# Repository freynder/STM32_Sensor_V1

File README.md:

# STM32 sensors board with RFM69(H)W footprint

First try on designing an STM32 board for running MySensors

## Top view

## Bottom view

## Early prototype top

## Early prototype bottom

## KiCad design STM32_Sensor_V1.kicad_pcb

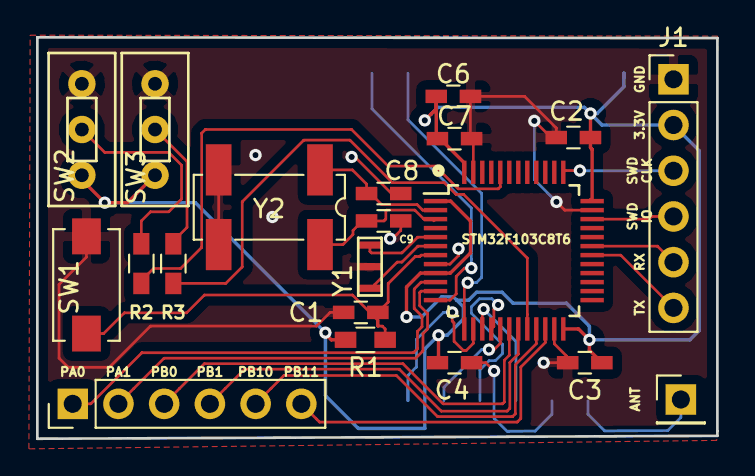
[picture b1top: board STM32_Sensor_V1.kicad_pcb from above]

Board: 2 copper layers, 37.8 x 22.3 mm, 21 parts (1 on the bottom side), 28 nets.

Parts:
C1: 1uF; C_0603_HandSoldering
C2, C3, C4, C6: 0.1uF; C_0603_HandSoldering
C7: 10uF; C_0603_HandSoldering
C8, C9: 10pF; C_0603_HandSoldering
J1: IO Header; Pin_Header_Straight_1x06_Pitch2.54mm
J2: Antenna; Pin_Header_Straight_1x01_Pitch2.54mm
J3: Pins breakout; Pin_Header_Straight_1x06_Pitch2.54mm
R1: 10K; R_0603_HandSoldering
R2, R3: 100K; R_0603_HandSoldering
SW1: SW_Push; SW_SPST_EVQPE1
SW2, SW3: SW_SPDT; SS-12D00
U1: STM32F103C8Tx; LQFP-48_7x7mm_Pitch0.5mm
U2: RFM69HW; HOPERF-RFM69HW
Y1: 8Mhz; CSTCE_G_RESONATOR
Y2: 32768Hz; Crystal_SMD_SeikoEpson_MC306-4pin_8.0x3.2mm_HandSoldering

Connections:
+3V3: C2.1, C3.1, C4.1, C6.1, C7.1, J1.2, R1.1, SW2.3, SW3.3, U1.1, U1.9, U1.24, U1.36, U1.48, U2.8
BOOT0: R2.2, U1.44
BOOT1: R3.2, U1.20
DIO0: U1.13, U2.2
GND: C1.2, C2.2, C3.2, C4.2, C6.2, C7.2, C8.2, C9.2, J1.1, SW1.1, SW2.1, SW3.1, U1.8, U1.23, U1.35, U1.47, U2.9, U2.11, Y1.2, Y2.2, Y2.3
MISO: U1.16, U2.13
MOSI: U1.17, U2.14
NSS: U1.14, U2.15
unnamed: C1.1, R1.2, SW1.2, U1.7
unnamed: J2.1, U2.10
unnamed: R2.1, SW2.2
unnamed: R3.1, SW3.2
OSC1: U1.5, Y1.1
OSC2: U1.6, Y1.3
PA0: J3.1, U1.10
PA1: J3.2, U1.11
PB0: J3.3, U1.18
PB1: J3.4, U1.19
PB10: J3.5, U1.21
PB11: J3.6, U1.22
RST: U1.12, U2.1
RTCOSC1: C8.1, U1.2, Y2.1
RTCOSC2: C9.1, U1.3, Y2.4
RX: J1.5, U1.31
SCK: U1.15, U2.12
SWDCLK: J1.3, U1.37
SWDIO: J1.4, U1.34
TX: J1.6, U1.30

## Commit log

2018-06-25 initial
2018-06-25 Added images
